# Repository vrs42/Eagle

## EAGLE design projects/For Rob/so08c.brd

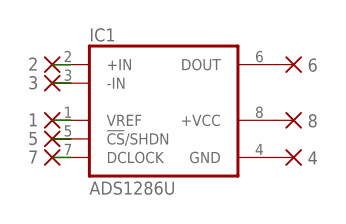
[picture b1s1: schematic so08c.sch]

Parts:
1, 2, 3, 4, 5, 6, 7, 8: PAD-0360; 0360
IC1: ADS1286U; SO08

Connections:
unnamed: 8.P$1, IC1.8 (+VCC)
unnamed: 7.P$1, IC1.7 (DCLOCK)
unnamed: 5.P$1, IC1.5 (!CS!/SHDN)
unnamed: 1.P$1, IC1.1 (VREF)
unnamed: 2.P$1, IC1.2 (+IN)
unnamed: 3.P$1, IC1.3 (-IN)
unnamed: 4.P$1, IC1.4 (GND)
unnamed: 6.P$1, IC1.6 (DOUT)

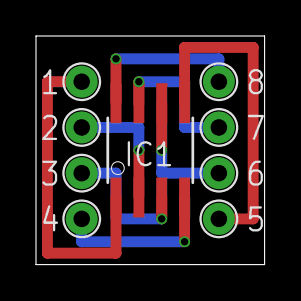
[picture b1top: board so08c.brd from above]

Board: 2 copper layers, 12.7 x 12.7 mm, 9 parts (0 on the bottom side), 8 nets.

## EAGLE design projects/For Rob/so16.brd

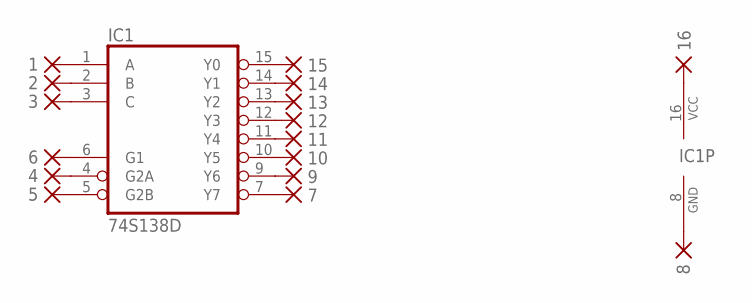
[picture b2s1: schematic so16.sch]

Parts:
1, 2, 3, 4, 5, 6, 7, 8, 9, 10, 11, 12, 13, 14, 15, 16: PAD-0360; 0360
IC1: 74S138D; SO16

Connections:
unnamed: 16.P$1, IC1.16 (VCC)
unnamed: 8.P$1, IC1.8 (GND)
unnamed: 6.P$1, IC1.6 (G1)
unnamed: 2.P$1, IC1.2 (B)
unnamed: 3.P$1, IC1.3 (C)
unnamed: 1.P$1, IC1.1 (A)
unnamed: 5.P$1, IC1.5 (G2B)
unnamed: 7.P$1, IC1.7 (Y7)
unnamed: 4.P$1, IC1.4 (G2A)
unnamed: 9.P$1, IC1.9 (Y6)
unnamed: 15.P$1, IC1.15 (Y0)
unnamed: 14.P$1, IC1.14 (Y1)
unnamed: 10.P$1, IC1.10 (Y5)
unnamed: 11.P$1, IC1.11 (Y4)
unnamed: 12.P$1, IC1.12 (Y3)
unnamed: 13.P$1, IC1.13 (Y2)

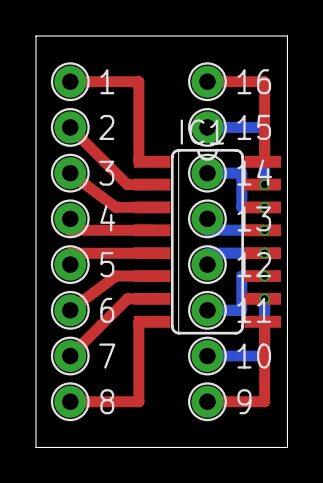
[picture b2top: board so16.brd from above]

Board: 2 copper layers, 14.0 x 22.9 mm, 17 parts (0 on the bottom side), 16 nets.

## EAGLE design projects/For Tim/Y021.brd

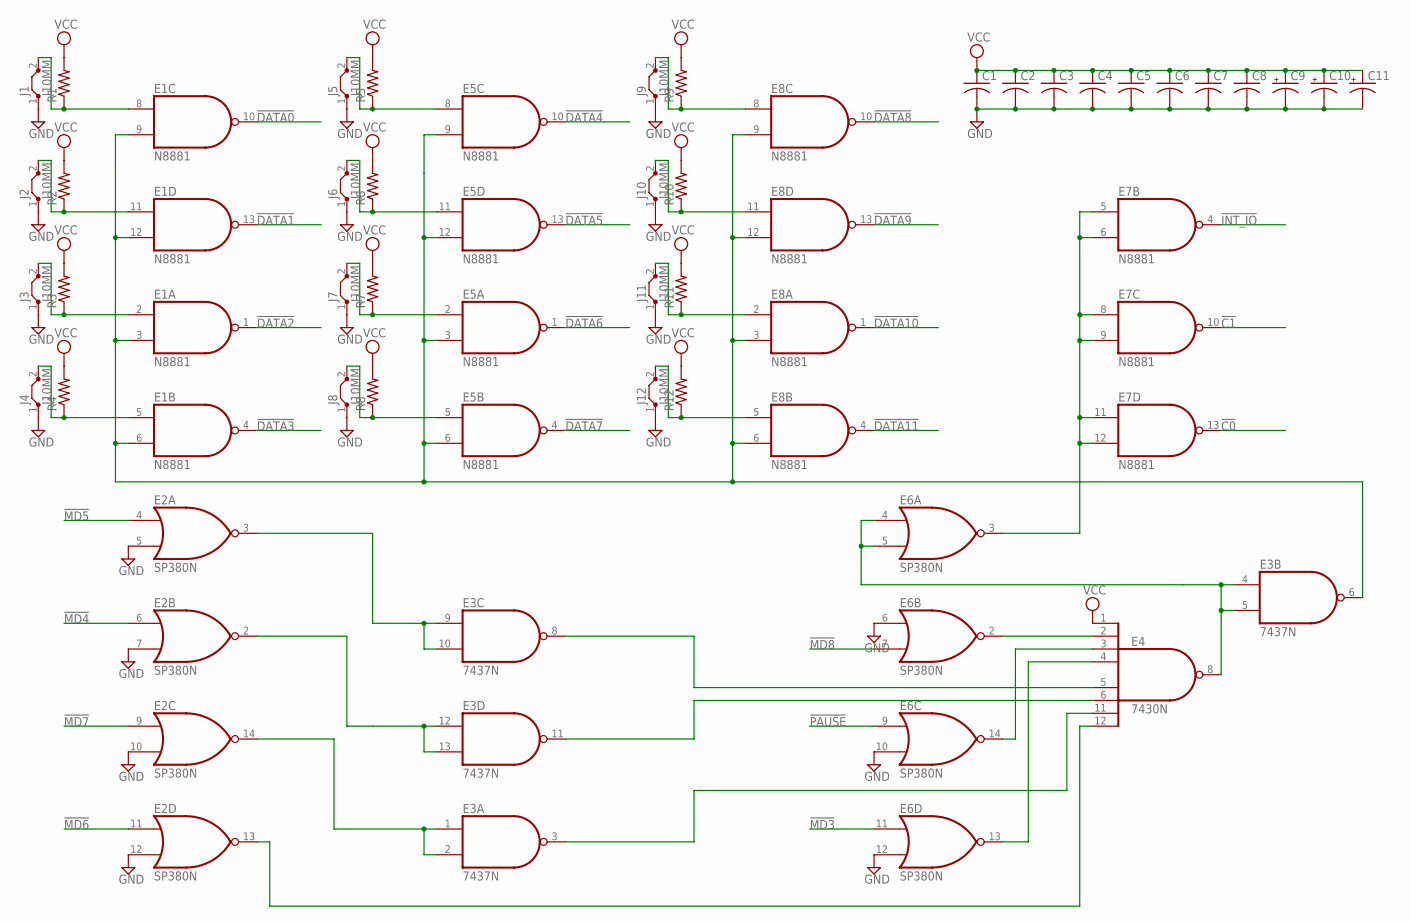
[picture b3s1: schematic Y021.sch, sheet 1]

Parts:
C1, C2, C3, C4, C5, C6, C7, C8: C-US050-025X075; C050-025X075
C9, C10, C11: CPOL-USE22-6AXIAL; E22-6
E1, E5, E7, E8: N8881; DIL14
E2, E6: SP380N; DIL14
E3: 7437N; DIL14
E4: 7430N; DIL14
J1, J2, J3, J4, J5, J6, J7, J8, J9, J10, J11, J12: J10MM; 10
R1, R2, R3, R4, R5, R6, R7, R8, R9, R10, R11, R12: R-US_0207/10; 0207/10

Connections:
!C0: E7.13 (O); also elsewhere on the board
!C1: E7.10 (O); also elsewhere on the board
!DATA0: E1.10 (O); also elsewhere on the board
!DATA1: E1.13 (O); also elsewhere on the board
!DATA2: E1.1 (O); also elsewhere on the board
!DATA3: E1.4 (O); also elsewhere on the board
!DATA4: E5.10 (O); also elsewhere on the board
!DATA5: E5.13 (O); also elsewhere on the board
!DATA6: E5.1 (O); also elsewhere on the board
!DATA7: E5.4 (O); also elsewhere on the board
!DATA8: E8.10 (O); also elsewhere on the board
!DATA9: E8.13 (O); also elsewhere on the board
!DATA10: E8.1 (O); also elsewhere on the board
!DATA11: E8.4 (O); also elsewhere on the board
!INT_IO: E7.4 (O); also elsewhere on the board
!MD3: E6.11 (I0); also elsewhere on the board
!MD4: E2.6 (I0); also elsewhere on the board
!MD5: E2.4 (I0); also elsewhere on the board
!MD6: E2.11 (I0); also elsewhere on the board
!MD7: E2.9 (I0); also elsewhere on the board
!MD8: E6.7 (I1); also elsewhere on the board
!PAUSE: E6.9 (I0); also elsewhere on the board
GND: C1.2, C2.2, C3.2, C4.2, C5.2, C6.2, C7.2, C8.2, C9.-, C10.-, C11.-, E1.7 (GND), E2.1 (GND), E2.5 (I1), E2.7 (I1), E2.10 (I1), E2.12 (I1), E3.7 (GND), E4.7 (GND), E5.7 (GND), E6.1 (GND), E6.6 (I0), E6.10 (I1), E6.12 (I1), E7.7 (GND), E8.7 (GND), J1.1, J2.1, J3.1, J4.1, J5.1, J6.1, J7.1, J8.1, J9.1, J10.1, J11.1, J12.1; also elsewhere on the board
unnamed: E1.2 (I0), J3.2, R3.1
unnamed: E1.3 (I1), E1.6 (I1), E1.9 (I1), E1.12 (I1), E3.6 (O), E5.3 (I1), E5.6 (I1), E5.9 (I1), E5.12 (I1), E8.3 (I1), E8.6 (I1), E8.9 (I1), E8.12 (I1)
unnamed: E1.11 (I0), J2.2, R2.1
unnamed: E6.3 (O), E7.5 (I0), E7.6 (I1), E7.8 (I0), E7.9 (I1), E7.11 (I0), E7.12 (I1)
unnamed: E1.8 (I0), J1.2, R1.1
unnamed: E5.2 (I0), J7.2, R7.1
unnamed: E1.5 (I0), J4.2, R4.1
unnamed: E5.8 (I0), J5.2, R5.1
unnamed: E5.11 (I0), J6.2, R6.1
unnamed: E5.5 (I0), J8.2, R8.1
unnamed: E8.8 (I0), J9.2, R9.1
unnamed: E8.5 (I0), J12.2, R12.1
unnamed: E8.2 (I0), J11.2, R11.1
unnamed: E8.11 (I0), J10.2, R10.1
unnamed: E4.2 (I1), E6.2 (O)
unnamed: E4.3 (I2), E6.14 (O)
unnamed: E3.4 (I0), E3.5 (I1), E4.8 (O), E6.4 (I0), E6.5 (I1)
unnamed: E4.4 (I3), E6.13 (O)
unnamed: E3.8 (O), E4.5 (I4)
unnamed: E3.11 (O), E4.6 (I5)
unnamed: E2.13 (O), E4.12 (I7)
unnamed: E3.3 (O), E4.11 (I6)
unnamed: E2.3 (O), E3.9 (I0), E3.10 (I1)
unnamed: E2.2 (O), E3.12 (I0), E3.13 (I1)
unnamed: E2.14 (O), E3.1 (I0), E3.2 (I1)
VCC: C1.1, C2.1, C3.1, C4.1, C5.1, C6.1, C7.1, C8.1, C9.+, C10.+, C11.+, E1.14 (VCC), E2.8 (VCC), E3.14 (VCC), E4.1 (I0), E4.14 (VCC), E5.14 (VCC), E6.8 (VCC), E7.14 (VCC), E8.14 (VCC), R1.2, R2.2, R3.2, R4.2, R5.2, R6.2, R7.2, R8.2, R9.2, R10.2, R11.2, R12.2; also elsewhere on the board

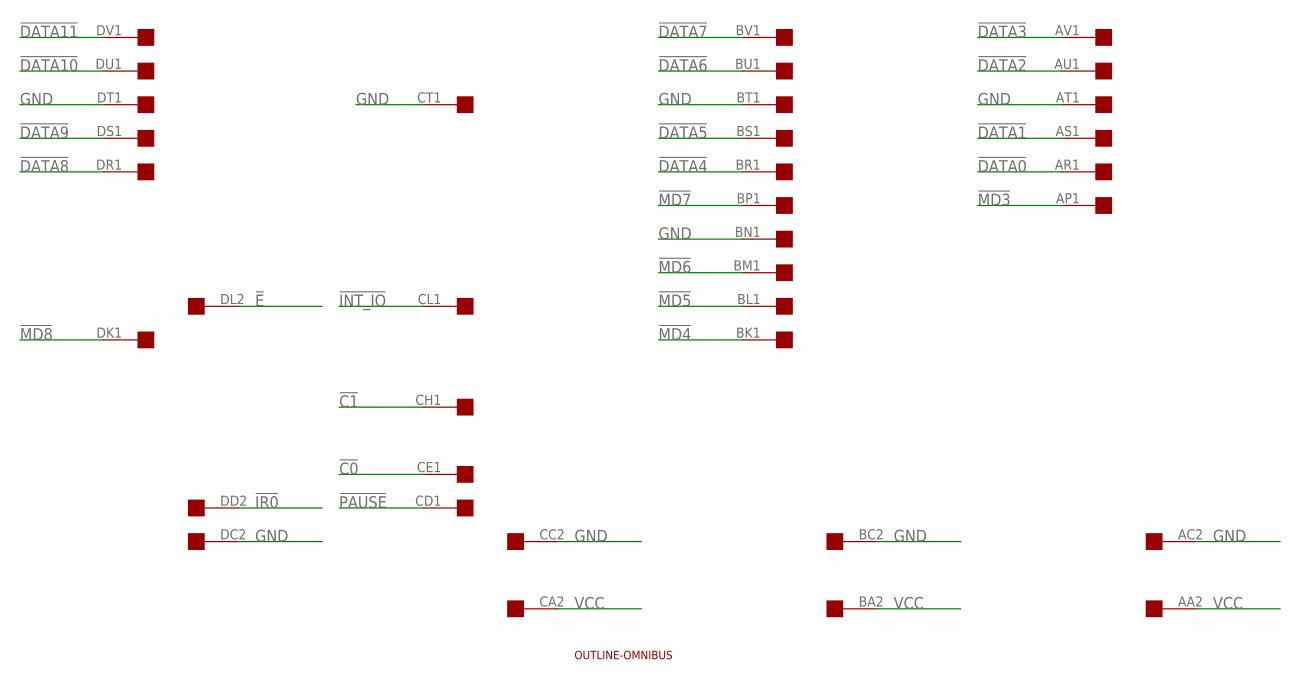
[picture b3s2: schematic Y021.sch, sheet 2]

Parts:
U$1: OUTLINE-OMNIBUS; OMNIBUS
U$2: QUAD; EDGE-CON8

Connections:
!C0: U$2.CE1; also elsewhere on the board
!C1: U$2.CH1; also elsewhere on the board
!DATA0: U$2.AR1; also elsewhere on the board
!DATA1: U$2.AS1; also elsewhere on the board
!DATA2: U$2.AU1; also elsewhere on the board
!DATA3: U$2.AV1; also elsewhere on the board
!DATA4: U$2.BR1; also elsewhere on the board
!DATA5: U$2.BS1; also elsewhere on the board
!DATA6: U$2.BU1; also elsewhere on the board
!DATA7: U$2.BV1; also elsewhere on the board
!DATA8: U$2.DR1; also elsewhere on the board
!DATA9: U$2.DS1; also elsewhere on the board
!DATA10: U$2.DU1; also elsewhere on the board
!DATA11: U$2.DV1; also elsewhere on the board
!E: U$2.DL2
!INT_IO: U$2.CL1; also elsewhere on the board
!IR0: U$2.DD2
!MD3: U$2.AP1; also elsewhere on the board
!MD4: U$2.BK1; also elsewhere on the board
!MD5: U$2.BL1; also elsewhere on the board
!MD6: U$2.BM1; also elsewhere on the board
!MD7: U$2.BP1; also elsewhere on the board
!MD8: U$2.DK1; also elsewhere on the board
!PAUSE: U$2.CD1; also elsewhere on the board
GND: U$2.AC2, U$2.AT1, U$2.BC2, U$2.BN1, U$2.BT1, U$2.CC2, U$2.CT1, U$2.DC2, U$2.DT1; also elsewhere on the board
VCC: U$2.AA2, U$2.BA2, U$2.CA2; also elsewhere on the board

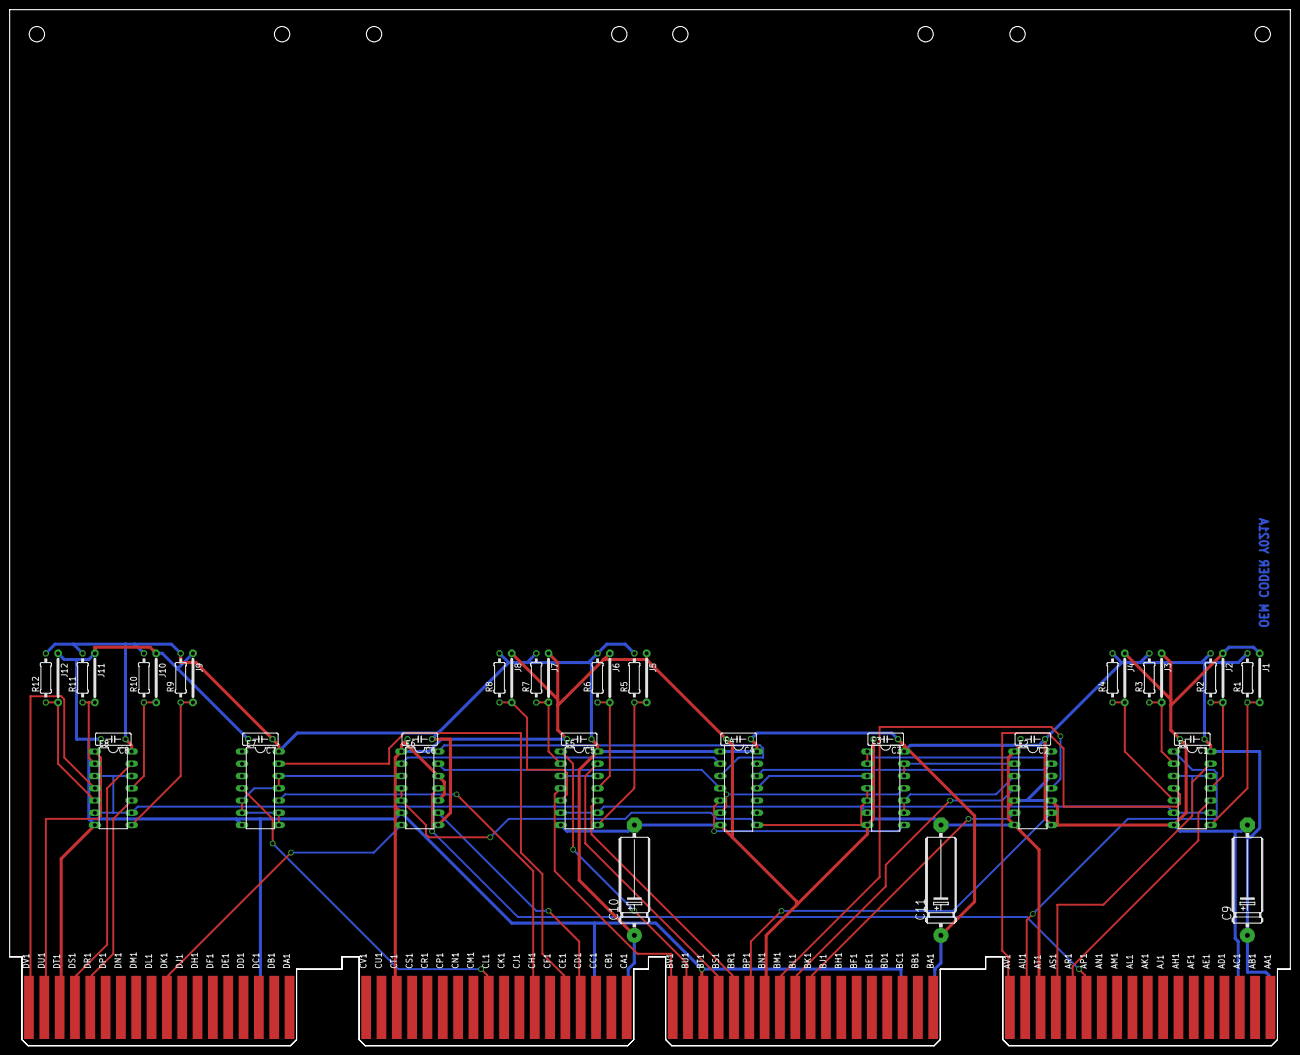
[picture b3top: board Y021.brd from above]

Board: 2 copper layers, 265.3 x 214.6 mm, 45 parts (0 on the bottom side), 49 nets.

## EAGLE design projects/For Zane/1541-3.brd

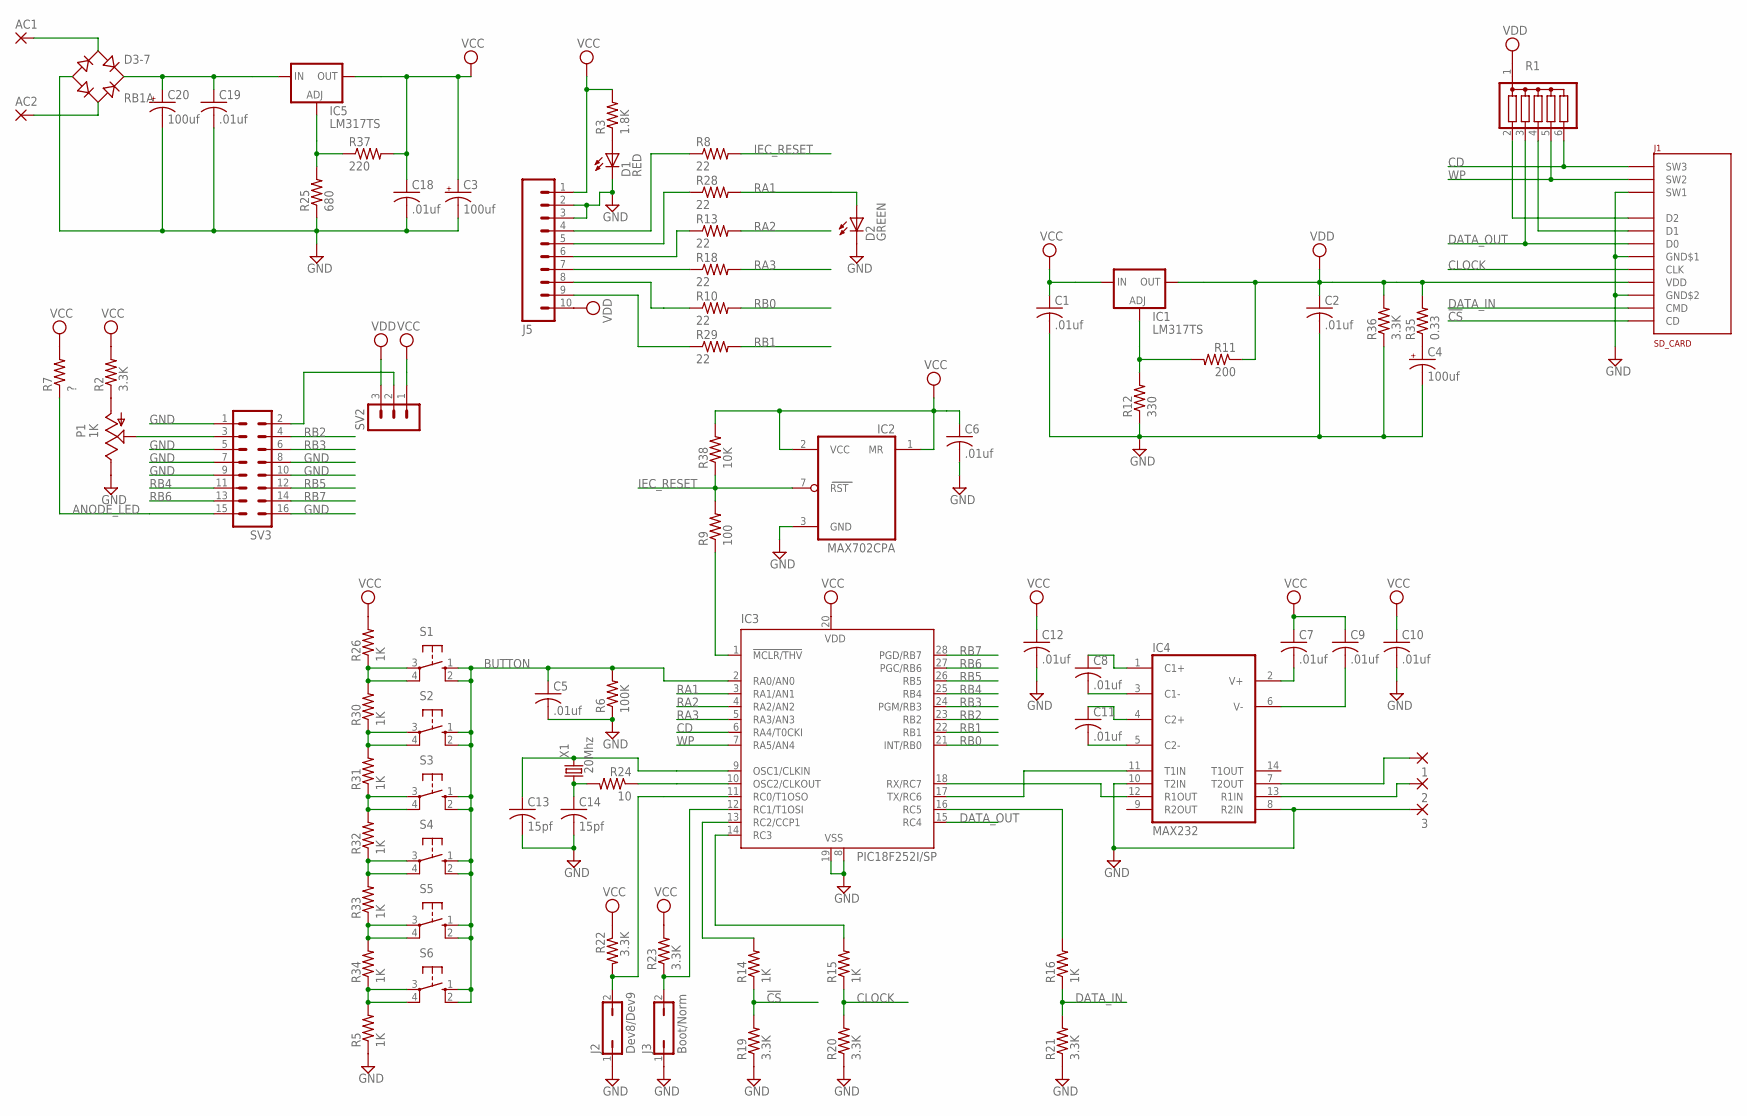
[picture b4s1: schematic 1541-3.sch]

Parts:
1, 2, 3: 2,15/1,0
AC1, AC2: 2,15/1,0
C1, C2, C5, C6, C7, C8, C9, C10, C11, C12, C18, C19: .01uf; C025-024X044
C3, C4, C20: 100uf; E2-5
C13, C14: 15pf; C025-024X044
D1: RED; LED3MM
D2: GREEN; LED3MM
D3-7: RB1A
IC1, IC5: LM317TS; 317TS
IC2: MAX702CPA; DIL08
IC3: PIC18F252I/SP; DIL28-3
IC4: MAX232; DIL16
J1: SD_CARD
J2: Dev8/Dev9; JP1
J3: Boot/Norm; JP1
J5: M10; 10P
P1: 1K; LI10
R1: G05R; SIL6
R2, R19, R20, R21, R22, R23, R36: 3.3K; 0207/2V
R3: 1.8K; 0207/2V
R5, R14, R15, R16, R26, R30, R31, R32, R33, R34: 1K; 0207/2V
R6: 100K; 0207/2V
R7: ?; 0207/2V
R8, R10, R13, R18, R28, R29: 22; 0207/2V
R9: 100; 0207/2V
R11: 200; 0207/2V
R12: 330; 0207/2V
R24: 10; 0207/2V
R25: 680; 0207/2V
R35: 0.33; 0207/2V
R37: 220; 0207/2V
R38: 10K; 0207/2V
S1, S2, S3, S4, S5, S6: 10-XX; B3F-10XX
SV2: MA03-1
SV3: ML16
X1: 20Mhz; HC49U70

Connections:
!CS: J1.DAT3 (CD), R14.1, R19.2
ANODE_LED: R7.1, SV3.15
BUTTON: C5.1, IC3.2 (RA0/AN0), R6.2, S1.1 (S), S1.2 (S1), S2.1 (S), S2.2 (S1), S3.1 (S), S3.2 (S1), S4.1 (S), S4.2 (S1), S5.1 (S), S5.2 (S1), S6.1 (S), S6.2 (S1)
CD: IC3.6 (RA4/T0CKI), J1.SW3, R1.6
CLOCK: J1.CLK, R15.1, R20.2
DATA_IN: J1.CMD, R16.1, R21.2
DATA_OUT: IC3.15 (RC4), J1.DAT0 (D0), R1.3
GND: 3.1, C1.2, C2.2, C3.-, C4.-, C5.2, C6.2, C10.2, C12.2, C13.2, C14.2, C18.2, C19.2, C20.-, D1.K (C), D2.K (C), D3-7.-, IC2.3 (GND), IC3.8 (VSS), IC3.19 (VSS), IC4.8 (R2IN), IC4.10 (T2IN), IC4.15 (GND), J1.SW1, J1.VSS$1 (GND$1), J1.VSS$2 (GND$2), J2.1, J3.1, J5.2, J5.3, P1.E, R5.1, R6.1, R12.1, R19.1, R20.1, R21.1, R25.1, R36.1, SV3.1, SV3.5, SV3.7, SV3.8, SV3.9, SV3.10, SV3.16
IEC_RESET: IC2.7 (RST), R8.2, R9.2, R38.1
unnamed: C4.+, R35.1
unnamed: J1.DAT2 (D2), R1.2
unnamed: J1.DAT1 (D1), R1.4
unnamed: J5.9, R29.1
unnamed: J5.8, R10.1
unnamed: J5.7, R18.1
unnamed: J5.4, R8.1
unnamed: J5.5, R28.1
unnamed: J5.6, R13.1
unnamed: D1.A, R3.1
unnamed: IC3.18 (RX/RC7), IC4.12 (R1OUT)
unnamed: IC3.14 (RC3), R15.2
unnamed: C14.1, R24.2, X1.1
unnamed: IC3.1 (!MCLR/THV), R9.1
unnamed: C11.1, IC4.4 (C2+)
unnamed: C11.2, IC4.5 (C2-)
unnamed: C8.2, IC4.3 (C1-)
unnamed: C8.1, IC4.1 (C1+)
unnamed: C7.2, IC4.2 (V+)
unnamed: C13.1, IC3.9 (OSC1/CLKIN), X1.2
unnamed: IC3.10 (OSC2/CLKOUT), R24.1
unnamed: IC3.12 (RC1/T1OSI), J3.2, R23.1
unnamed: IC3.11 (RC0/T1OSO), J2.2, R22.2
unnamed: IC3.13 (RC2/CCP1), R14.2
unnamed: IC3.16 (RC5), R16.2
unnamed: IC1.1 (ADJ), R11.2, R12.2
unnamed: IC3.17 (TX/RC6), IC4.11 (T1IN)
unnamed: R26.1, R30.2, S1.3, S1.4 (P1)
unnamed: R30.1, R31.2, S2.3, S2.4 (P1)
unnamed: R31.1, R32.2, S3.3, S3.4 (P1)
unnamed: R5.2, R34.1, S6.3, S6.4 (P1)
unnamed: R33.1, R34.2, S5.3, S5.4 (P1)
unnamed: R32.1, R33.2, S4.3, S4.4 (P1)
unnamed: P1.A, R2.1
unnamed: SV2.2, SV3.2
unnamed: P1.S, SV3.3
unnamed: C9.2, IC4.6 (V-)
unnamed: IC5.1 (ADJ), R25.2, R37.1
unnamed: AC1.1, D3-7.AC1
unnamed: C19.1, C20.+, D3-7.+, IC5.3 (IN)
unnamed: AC2.1, D3-7.AC2
unnamed: 2.1, IC4.13 (R1IN)
unnamed: 1.1, IC4.7 (T2OUT)
RA1: D2.A, IC3.3 (RA1/AN1), R28.2
RA2: IC3.4 (RA2/AN2), R13.2
RA3: IC3.5 (RA3/AN3), R18.2
RB0: IC3.21 (INT/RB0), R10.2
RB1: IC3.22 (RB1), R29.2
RB2: IC3.23 (RB2), SV3.4
RB3: IC3.24 (PGM/RB3), SV3.6
RB4: IC3.25 (RB4), SV3.11
RB5: IC3.26 (RB5), SV3.12
RB6: IC3.27 (PGC/RB6), SV3.13
RB7: IC3.28 (PGD/RB7), SV3.14
VCC: C1.1, C3.+, C6.1, C7.1, C9.1, C10.1, C12.1, C18.1, IC1.3 (IN), IC2.1 (MR), IC2.2 (VCC), IC3.20 (VDD), IC4.16 (VCC), IC5.2 (OUT), J5.1, R2.2, R3.2, R7.2, R22.1, R23.2, R26.2, R37.2, R38.2, SV2.1
VDD: C2.1, IC1.2 (OUT), J1.VDD, J5.10, R1.1, R11.1, R35.2, R36.2, SV2.3
WP: IC3.7 (RA5/AN4), J1.SW2, R1.5

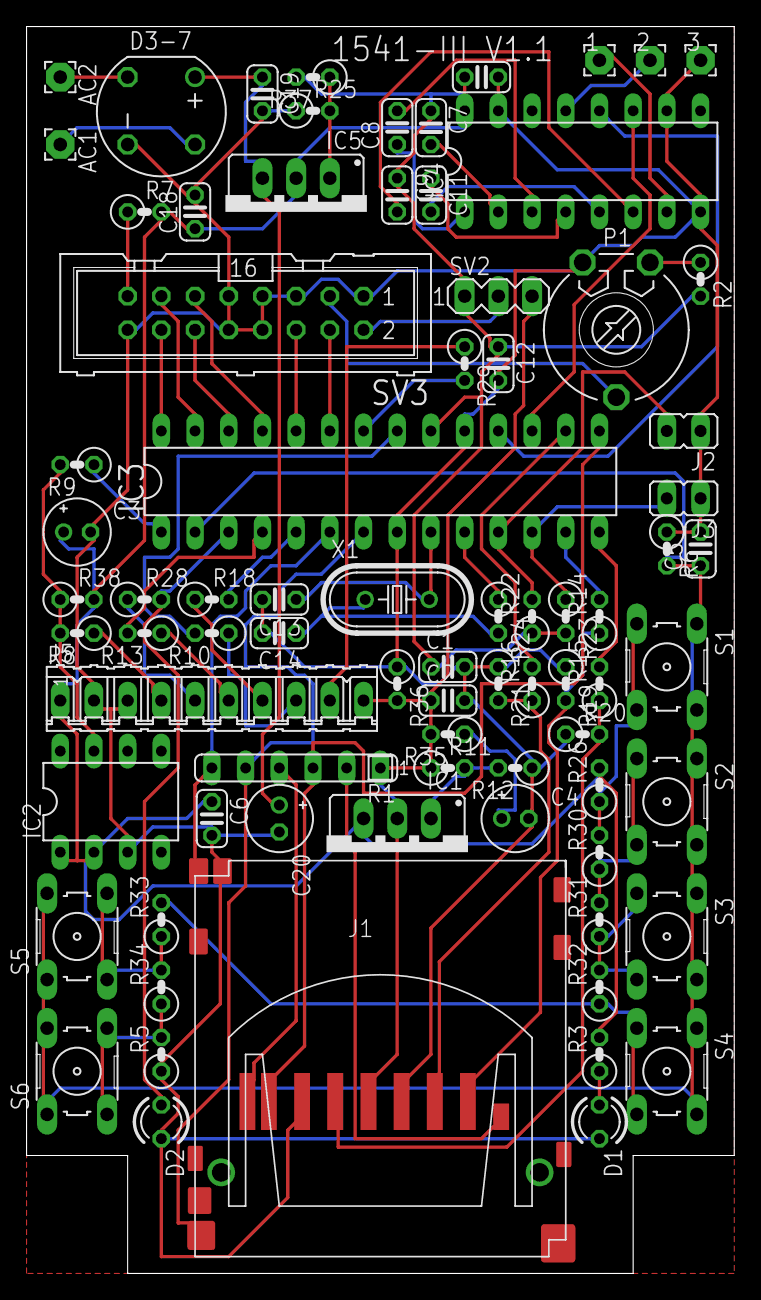
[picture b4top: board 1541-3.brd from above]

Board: 2 copper layers, 53.3 x 94.0 mm, 79 parts (0 on the bottom side), 66 nets.
